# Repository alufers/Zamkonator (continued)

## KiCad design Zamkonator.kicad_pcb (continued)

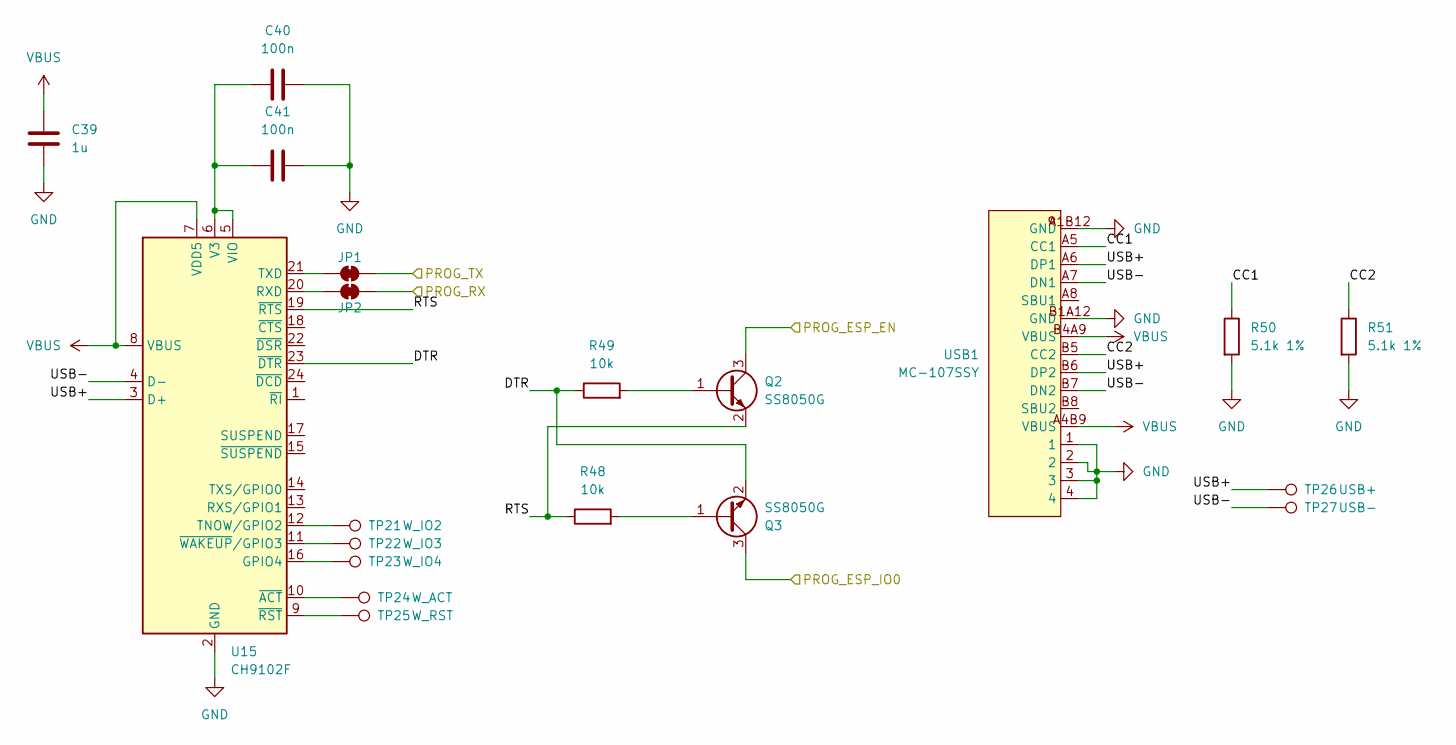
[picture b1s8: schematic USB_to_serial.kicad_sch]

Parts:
C39: 1u; C_0603_1608Metric; JLCPCB C559769
C40, C41: 100n; C_0603_1608Metric; JLCPCB C14663
JP1, JP2: SolderJumper_2_Bridged; SolderJumper-2_P1.3mm_Bridged_RoundedPad1.0x1.5mm
Q2, Q3: SS8050G; SOT-23; JLCPCB C164886
R48, R49: 10k; R_0603_1608Metric; JLCPCB C25804
R50, R51: 5.1k 1%; R_0603_1608Metric; JLCPCB C23186
TP21: W_IO2; TestPoint_Pad_D1.0mm
TP22: W_IO3; TestPoint_Pad_D1.0mm
TP23: W_IO4; TestPoint_Pad_D1.0mm
TP24: W_ACT; TestPoint_Pad_D1.0mm
TP25: W_RST; TestPoint_Pad_D1.0mm
TP26: USB+; TestPoint_Pad_D1.0mm
TP27: USB-; TestPoint_Pad_D1.0mm
U15: CH9102F; QFN-24-1EP_4x4mm_P0.5mm_EP2.6x2.6mm; JLCPCB C2858418
USB1: MC-107SSY; USB-TYPE-C-SMD_MC-107SSY; JLCPCB C3039307

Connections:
/ESP_EN: Q2.3 (C); also elsewhere on the board
/ESP_RX: JP1.2 (B); also elsewhere on the board
/ESP_TX: JP2.2 (B); also elsewhere on the board
/USB_to_serial/CC1: R50.1, USB1.A5 (CC1)
/USB_to_serial/CC2: R51.1, USB1.B5 (CC2)
/USB_to_serial/DTR: Q3.2 (E), R49.1, U15.23 (~DTR)
/USB_to_serial/PROG_ESP_IO0: Q3.3 (C); also elsewhere on the board
/USB_to_serial/RTS: Q2.2 (E), R48.1, U15.19 (~RTS)
/USB_to_serial/USB+: TP26.1 (1_1), U15.3 (D+), USB1.A6 (DP1), USB1.B6 (DP2)
/USB_to_serial/USB-: TP27.1 (1_1), U15.4 (D-), USB1.A7 (DN1), USB1.B7 (DN2)
GND: C39.1, C40.2, C41.2, R50.2, R51.2, U15.2 (GND), U15.25 (GND), USB1.1, USB1.2, USB1.3, USB1.4, USB1.A1B12 (GND), USB1.B1A12 (GND); also elsewhere on the board
unnamed: JP1.1 (A), U15.21 (TXD)
unnamed: JP2.1 (A), U15.20 (RXD)
unnamed: Q2.1 (B), R49.2
unnamed: Q3.1 (B), R48.2
unnamed: TP23.1 (1_1), U15.16 (GPIO4)
unnamed: TP21.1 (1_1), U15.12 (TNOW/GPIO2)
unnamed: C40.1, C41.1, U15.5 (VIO), U15.6 (V3)
unnamed: TP24.1 (1_1), U15.10 (~ACT)
unnamed: TP25.1 (1_1), U15.9 (~RST)
unnamed: TP22.1 (1_1), U15.11 (~WAKEUP/GPIO3)
VBUS: C39.2, U15.7 (VDD5), U15.8 (VBUS), USB1.A4B9 (VBUS), USB1.B4A9 (VBUS)

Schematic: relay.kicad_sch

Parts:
D20: 1N4007; D_SMA_Handsoldering; LCSC C7528875
K1: SRD-DC3V-SL-C; Relay_SPDT_SANYOU_SRD_Series_Form_C; LCSC C688864
Q1: DMG2302U; SOT-23; LCSC C460977
R43: 100K 1%; R_0603_1608Metric_Pad0.98x0.95mm_HandSolder; LCSC C2906980
R44: 1k; R_0603_1608Metric_Pad0.98x0.95mm_HandSolder; LCSC C22548

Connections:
+3.3V: D20.1 (K), K1.2; also elsewhere on the board
/RELAY_CTL: R43.1, R44.1; also elsewhere on the board
/R_C: K1.1; also elsewhere on the board
/R_NC: K1.4; also elsewhere on the board
/R_NO: K1.3; also elsewhere on the board
GND: Q1.2 (S), R43.2; also elsewhere on the board
unnamed: D20.2 (A), K1.5, Q1.3 (D)
unnamed: Q1.1 (G), R44.2

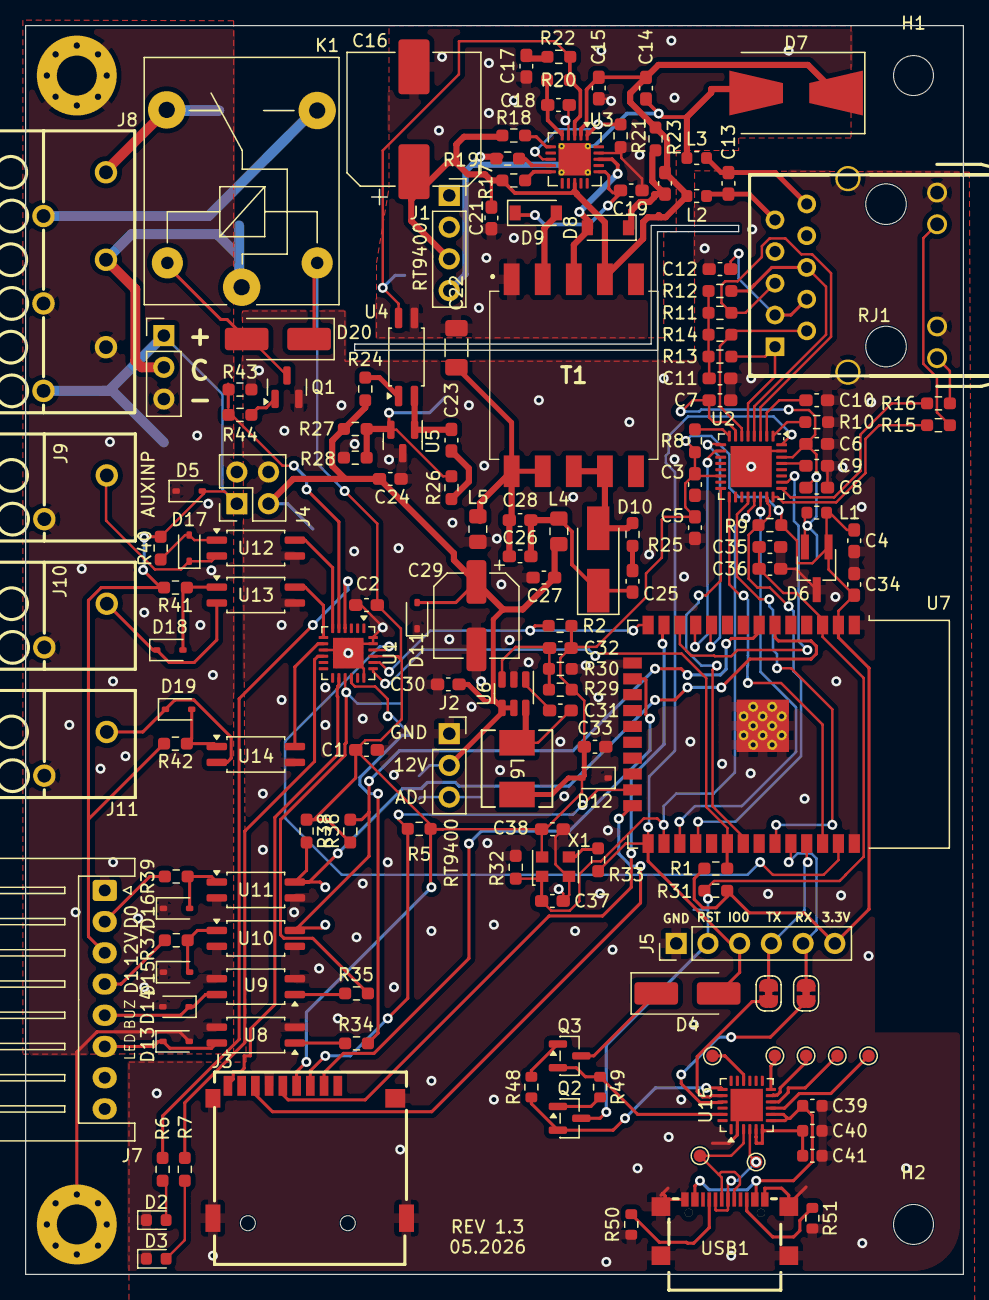
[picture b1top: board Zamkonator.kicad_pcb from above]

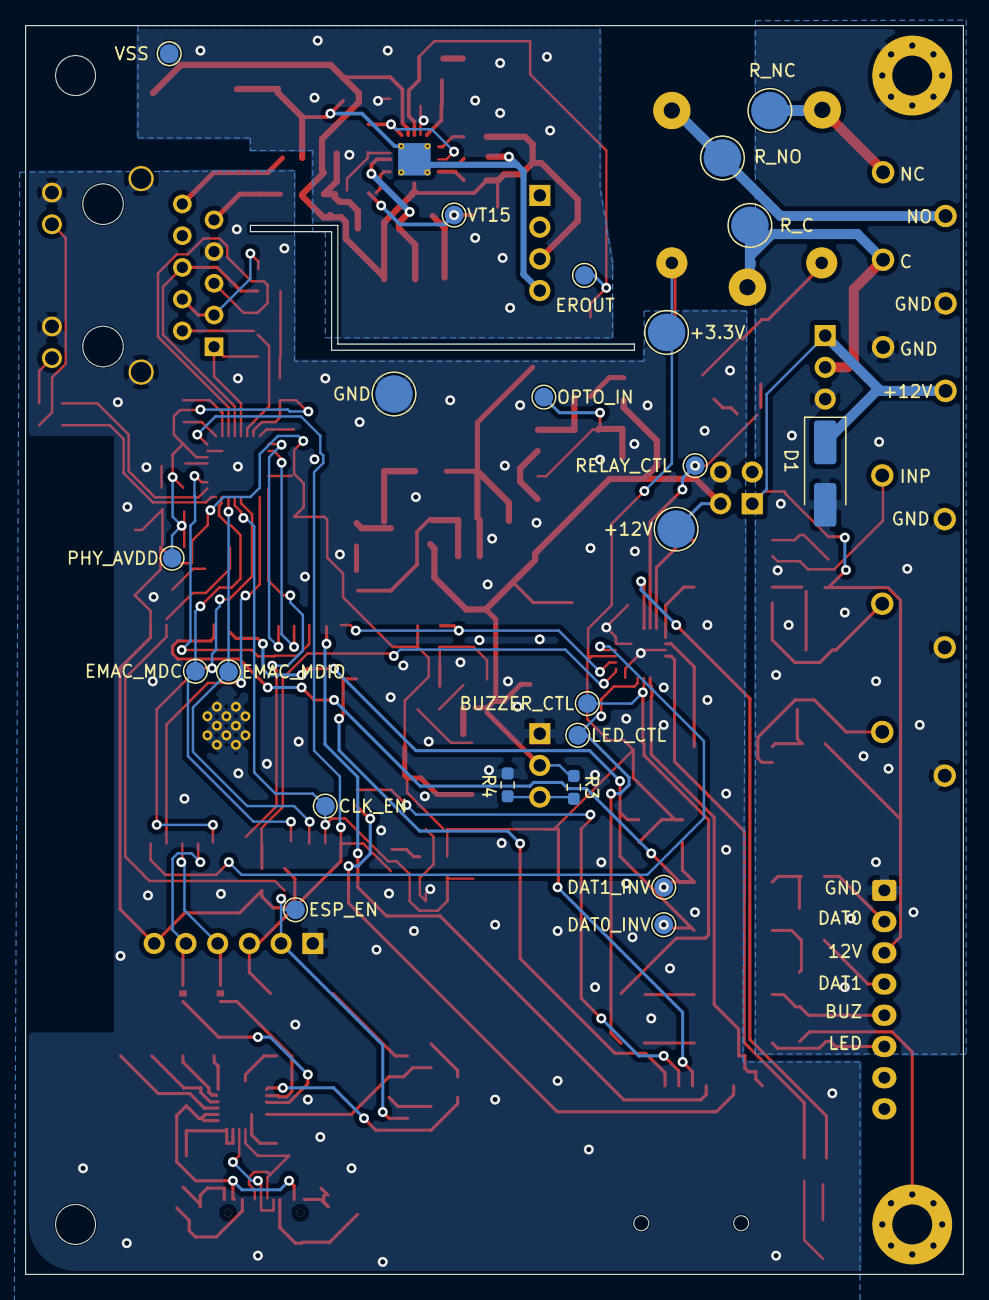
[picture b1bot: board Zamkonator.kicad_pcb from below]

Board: 2 copper layers, 75.1 x 100.0 mm, 182 parts (23 on the bottom side), 119 nets.

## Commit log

2022-10-18 finish shcematic
2022-10-23 feat: add more LCSC symbols
2022-10-23 Remove non-standard resistor
2022-10-27 fixup wrong resistor values
2022-11-01 Add the YAGEO script
2022-11-02 add basic nix firmware config
2022-11-02 Try some stuff with the flakes
2022-11-02 Add new nix configuration
2022-11-02 Add basic esp-idf structure
2022-11-02 Add basic spifs structure
2022-11-02 Add basic config maanagement
2022-11-02 feat: add basic NetworkManager skeleton
2022-11-02 Add apStarting to NetworkManager
2022-11-04 Finixsh XBus
2022-11-04 Add a readme and some docs
2022-12-05 Add some more footprints
2023-01-14 Add even more footprints
2023-01-15 basic ETH layout
2023-02-01 layout fixes
2023-02-10 Finish basic layout
2023-02-10 add screw holes
2023-02-10 tracks
2023-02-11 More tracks, before big change in layout...
2023-02-12 Finish layout
2023-02-12 add header labels
2023-02-13 Add testpoints, jumpers
2023-02-13 Update inductor footprint
2023-02-13 RT9400 module option added
2023-02-13 Finishing touches, rounded PCB
2023-02-13 adjust silkscreen
2023-02-13 Fixup module resolution in YAGEO
2023-02-13 Fixup diode footprint and add more LCSC numbers
2023-02-14 Add more LCSC markings, change to electrolytic caps :
2023-02-15 Switch to LCSC RJ45 socket
2023-02-17 Add missing files
2023-03-06 Silkscreen fixes
2023-03-19 Add stuff
2024-10-31 Update kicad files
2024-11-19 Add testfw
2024-11-19 Increaste timeout, add wait before reboot
2024-11-20 Kicad updates, added missing resistances
2024-12-29 Add macOS stuff to gitignore
2024-12-29 use contributed symbol for RTL8021F
2025-09-05 BOM updates & schematic fixes
2025-09-28 fix PoE transofrmer polarity, add more relay outputs
2025-10-03 DO the bulk of rev 1.2 layout
2025-10-03 Cleanup footprints
2025-10-03 Use kicad symbol for the optotransistor
2025-10-03 Remove custom library for EL3H7, use the kicad one.
2025-10-03 Use kicad built-in symbol for AN431.
2025-10-03 remove custom footprint for Si3404
2025-10-03 Update crystal LCSC number, use built-in footprint
2025-10-03 remove custom oscillator symbol, add 3d model
2025-10-03 Add optocoupler 3d model
2025-10-03 Add PoE transformer 3D model
2025-10-03 Use cheaper SD card socket
2025-10-03 Add all missing 3D models
2025-10-04 Prepare push in connectors, add aux input
2025-10-06 try playing around with the output screw terminals
2025-10-08 Finish the schematic maybe
2025-10-08 Finish preliminary routing
2025-10-08 Finish routing
2026-03-25 BOM updates
2026-05-09 misc updates, extend board
2026-05-26 Zamkonator rev 1.3
2026-06-29 Rev 1.3, BOM optimizations
